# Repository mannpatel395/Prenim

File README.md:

# Prenim
A gamimg controller with switches, joystick and mcu as sparkfun pro micro. I am using cpp for a code.

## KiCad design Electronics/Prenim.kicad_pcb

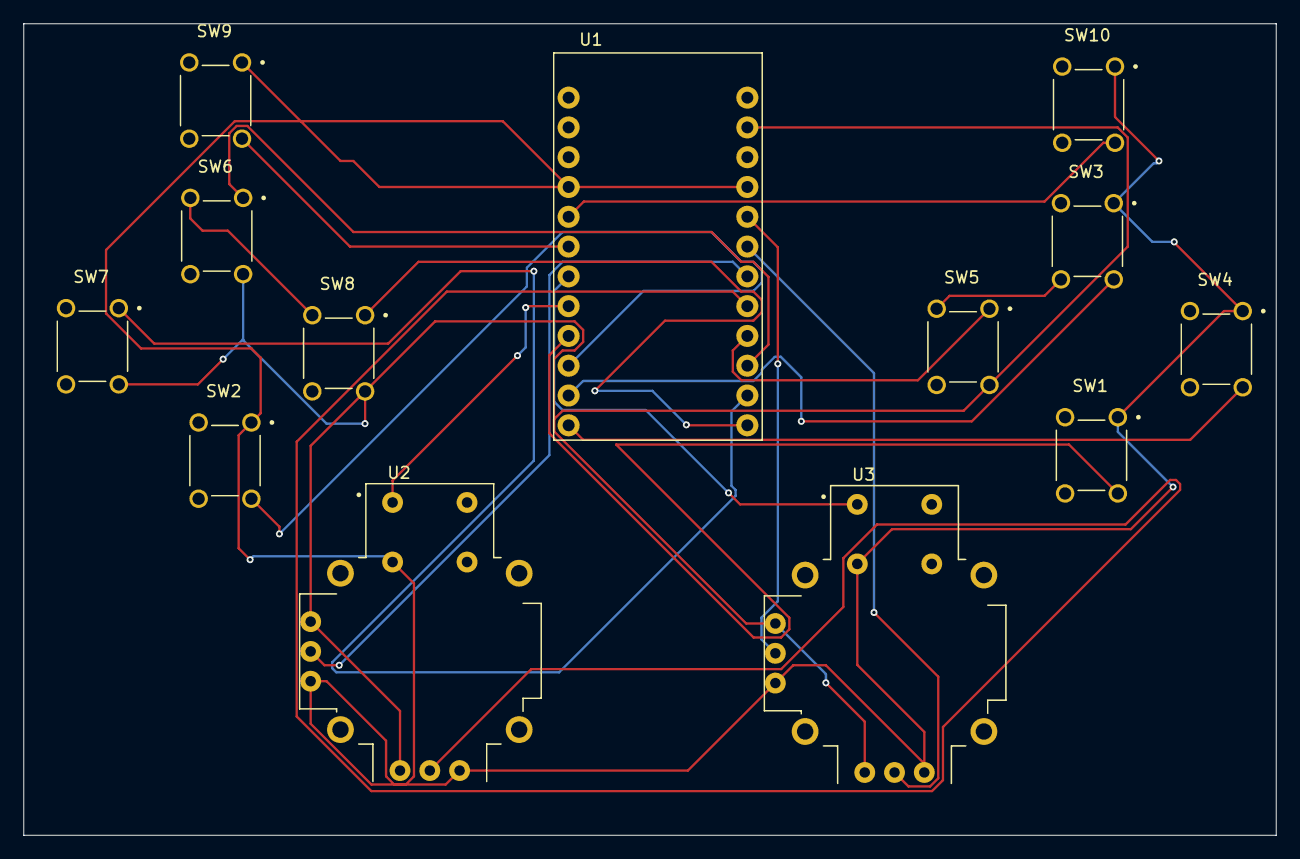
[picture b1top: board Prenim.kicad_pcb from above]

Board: 2 copper layers, 106.8 x 69.2 mm, 13 parts (0 on the bottom side), 18 nets.

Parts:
SW1, SW2, SW3, SW4, SW5, SW6, SW7, SW8, SW9, SW10: SW_Push; SW_FSM8JH
U1: Spark; MODULE_DEV-12587
U2, U3: COM-09032; XDCR_COM-09032

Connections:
/JSW1: U1.8 (5), U2.B1A (SEL+)
/JSW2: U1.7 (4), U3.B1A (SEL+)
/L1: SW9.2, U1.6 (3)
/R1: SW10.2, U1.5 (2)
/VRx1: U1.17 (A0), U2.H2 (H)
/VRx2: U1.19 (A2), U3.H2 (H)
/VRy1: U1.18 (A1), U2.V2 (V)
/VRy2: U1.20 (A3), U3.V2 (V)
/gnd: SW1.1, SW2.1, SW3.1, SW4.1, SW9.1, SW10.1, U1.4 (gnd), U1.21 (vcc), U2.B2A (SEL-), U2.H3 (H-), U2.V3 (V-), U3.B2A (SEL-), U3.H3 (H-), U3.V3 (V-)
/vcc: SW5.2, SW6.2, SW7.2, SW8.2, U1.23 (GND), U2.H1 (H+), U2.V1 (V+), U3.H1 (H+), U3.V1 (V+)
unnamed: SW6.1, U1.15
unnamed: SW1.2, U1.9 (6)
unnamed: SW2.2, U1.10 (7)
unnamed: SW3.2, U1.11 (8)
unnamed: SW4.2, U1.12 (9)
unnamed: SW8.1, U1.13 (10)
unnamed: SW5.1, U1.16 (14)
unnamed: SW7.1, U1.14 (16)
